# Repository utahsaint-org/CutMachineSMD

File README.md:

# CutMachineSMD

The Resistor and LED Cutting machine is a community project to make mass-production of small SMD components cut to specific unit sizes faster and easier to make for our highly popular MiniBadge initiatives and standards.  This machine has been used in mass-production and works great for feeding and cutting several component types.

#### Key Features
- SMD Tape Cutting
- Custom Menu-Driven Calibration Settings
- Test Cutting and Program Cutting
- Sharpie Attachment to allow color-coding of components as they are cut
- Community Contribution

# Parts List:  

For convenience I have an Amazon List for most parts: https://a.co/ecXTVj9

- 2020 Extruded Aluminium cut to
  - 2x 30cm - Top/Bottom
  - 3x 26cm - Verticals
  - 2x 20cm - Legs
  - 1x 155mm - Horizontal Crossmember
  - 1x 155mm - Roll Attachment Crossmember (Optional)
- 2020 Series Connectors and Corner Bracket Set (30 Piece)
- Bracket L-Type Internal Connectors for 2020 Series
- 4x 2020 Series Rubber Feet
- Stepper Motors
  - NEMA23 4.2Amp Motor (StepperOnline 23HS45-4204S)
  - NEMA17 1.2Amp Motor (StepperOnline 17HS19-2004S)
- Motor Drivers
  - 1x EASON Stepper Motor Driver TB6600 4A
  - 2x Stepper Motor Driver DRV8825
- Cutting Blades - 9mm Knife Replacement Blade Cartridge
- Electronics
  - Arduino Uno R3 or similar device.
  - HiLetgo CNC Drive Expansion Board (CNC Shield)
  - 2.42" 128x64 OLED LCD Display (SSD1309) i2C
- M3 Hardware
  - Assorted M2 Length Screws, Nuts, Washers
  - Assorted M3 Length Screws, Nuts, Washers
  - Assorted M5 Length Screws, Nuts, Washers
  - M3 Lever Steering Linkage
  - M3 Link Strut shaft 35mm
- 1x Miniature Linear Sliding Guideway Rail 150mm
- Power Supplies
  - 12VDC 15A Linear Power Supply
  - 12VDC to 5VDC Stepdown Regulator to power the Arduino (Optional)
- Components for PCBs ([Digikey](https://digikey.com)/[Mouser](https://mouser.com) or Similar)
  - 4x 6mm THT PushButton Switchs
  - 6x 10KΩ SMD  1206 Resistors
  - 1x 220Ω SMD  1206 Resistor
  - 1x 2.2KΩ SMD 1206 Resistor
  - 7+ Position Right-Angle PIN Headers
  - 3+ Position Straight PIN Headers
- PCBs Ordered (JLC_PCB or Similar)
  - [1x Button_Board](https://github.com/utahsaint-org/CutMachineSMD/tree/main/CuttingMachine_PCB/Buttons/Gerbers) 
  - [2x Sensor_Board](https://github.com/utahsaint-org/CutMachineSMD/tree/main/CuttingMachine_PCB/Sensor/Gerbers)
    
# Setup and Configuration

### OLED Screen Modification
The OLED screen typically comes configured for SPI interface, and we are using I2C protocol in this project.   As such, you will need to modify the OLED screen by bridging several solder pads to put the screen into I2C configuration.   You will need to disconnect the ribbon-cable and underneath you will need to bridge the solder pads labeled: R9, R10, R11, R12.  You will also need to remove the Resistor labeled R8. (Follow the published instructions for the screen to make this modification)

### Building the Framework
The Framework for the machine is fairly stratight-forward.  The 30cm struts are mounted as the top and bottom rails.  Use normal corner attachments to make the connections.  The 26cm vertical struts are attached with one in the middle and the other two are attached on the edges to make a 30cm x 30cm frame.  The center vertical is attached at 105mm spacing from center to center or 85mm Internal spacing.  You can use the Acrylic Cut Head mount as the spacing guide.   Lastly the cross-member can be attached at the approximate horizontal mid-point (125mm internal spacing).  20cm Legs are mounted horizontally outside the frame for stability.  The frame with mounted motors becomes back-heavy so I personally offset the legs to favor the back side for better support.

### Power Supply
Picking the right power-supply is an important aspect of any Stepper Motor configuration.   For this machine I used a 12v 15A capable power supply.   This provided all of the power I needed to run both motors and the arduino electronics.

### 3D Printing
Several of the STL designs need **supports** to be printed to ensure they are printed correctly.
NOTE: There are two Cut Heads.  One for Resistors and one for LEDs.

### Assembly
Here is what you are building:

- Build the Framework as described above.
- Attach the AcrylicCutHead on the Back Side of the machine

- Attach a RazorBlade to the Printed CutHead on the outside
  - Bottom Screw goes THRU the hole on the blade
  - Top Screw squeezes the blade to the head using a washer

- Attach the Razor CutHead to the Slider Rail
- Attach the FeedHead to the center rails (Horizontal and Vertical)
  - Align the razor to the slit of the Feedhead
- Attach and Connect the Display (See connections diagram)

### Firmware and Flashing
The Firmware is available in the repo.  Use the Arduino IDE application to program the Arduino board.  There are several sources of documentation or videos that can instruct you on how to install and use this program.  If you have issues, limited technical support is available on the <a href=https://discord.gg/saintcon>SAINTCON Discord Server</a> #minibadge-creators

You will need to install the following libraries:
- Adafruit GFX
- Adafruit SSD1306 Display

**Board Type should be Arduino Uno (R3)**

Open the *CuttingMachine_Firmware.ino* in the Arduino IDE program
Compile and upload the Firmware using the appropriate COM Port

### Connections
Connections for all of the components are outlined in the diagram below.

### PCB Boards
The PCB Boards Gerbers are included in this repo.  The following instructions will help you assemble the boards and connect them properly.

#### Button_Board
- R1, R2, R3, R4 are all **10k Ohm** resistors.
- Buttons are THT 6mm Momentary Switch.
- Right-angle PIN HEADERS are suggested exiting out the back.
- Use a Solder Jumper to connect either 5v or 3v3. (Recommended you use 3v3)
- Attach the Board with M2 Screws/Bolts to the Display Controller.
- Attach the Connectors to CNC Shield as labeled in the Connections Diagram.

#### Sensor_Board
- R1 is 10K Ohm
- R2 is 470 Ohm (if using it as presence sensor)
- R2 is 2.2K Ohm (If used as tape position sensor)
- PIN HEADERS are 3 Position
- Attach the Board with the M5 Screw to the FeedHead

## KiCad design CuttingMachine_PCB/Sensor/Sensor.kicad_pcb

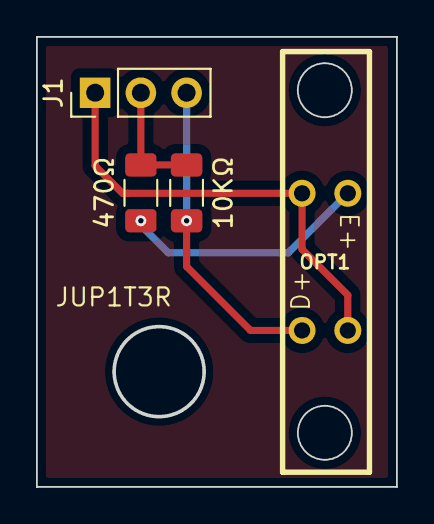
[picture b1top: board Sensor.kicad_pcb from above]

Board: 2 copper layers, 20.0 x 25.0 mm, 4 parts (0 on the bottom side), 4 nets.

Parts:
10KΩ: 220; R_1206_3216Metric_Pad1.30x1.75mm_HandSolder
470Ω: 10k; R_1206_3216Metric_Pad1.30x1.75mm_HandSolder
J1: Conn_01x03_Pin; PinHeader_1x03_P2.54mm_Vertical
OPT1: MOC7811

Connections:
unnamed: J1.1, OPT1.2 (E-), OPT1.4 (D-)
unnamed: 10KΩ.1, 470Ω.1, J1.2
unnamed: 10KΩ.2, J1.3, OPT1.3 (D+)
unnamed: 470Ω.2, OPT1.1 (E+)

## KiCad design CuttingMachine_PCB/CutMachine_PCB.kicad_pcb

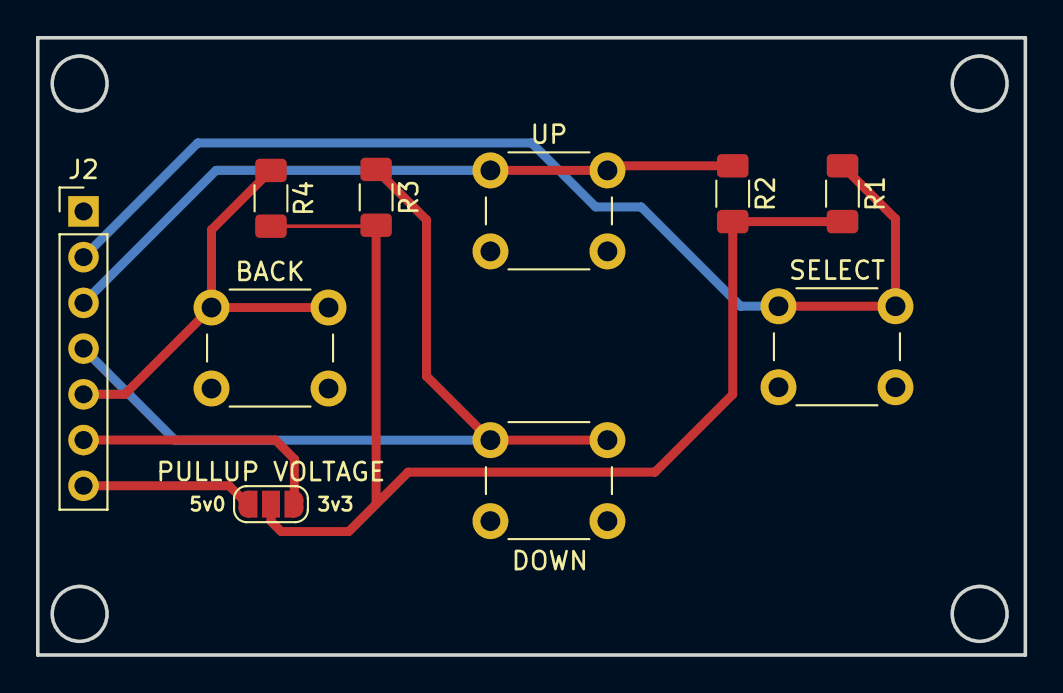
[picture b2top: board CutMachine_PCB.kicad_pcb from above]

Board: 2 copper layers, 54.9 x 34.3 mm, 10 parts (0 on the bottom side), 8 nets.

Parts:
BACK: BACK; SW_PUSH_6mm_H4.3mm
J2: Conn_01x07_Pin; PinHeader_1x07_P2.54mm_Vertical
PULLUP VOLTAGE: SolderJumper_3_Open; SolderJumper-3_P1.3mm_Open_RoundedPad1.0x1.5mm_NumberLabels
R1, R2, R3, R4: PULLUP; R_1206_3216Metric_Pad1.30x1.75mm_HandSolder
SELECT: SELECT; SW_PUSH_6mm_H4.3mm
SW3: DOWN; SW_PUSH_6mm_H4.3mm
UP: UP; SW_PUSH_6mm_H4.3mm

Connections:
+3.3V: J2.6, PULLUP VOLTAGE.3 (B)
+5V: J2.7, PULLUP VOLTAGE.1 (A)
GND: BACK.2, J2.1, SELECT.2, SW3.2, UP.2
unnamed: J2.2, R1.1, SELECT.1
unnamed: J2.3, R2.1, UP.1
unnamed: J2.4, R3.1, SW3.1
unnamed: BACK.1, J2.5, R4.1
unnamed: PULLUP VOLTAGE.2 (C), R1.2, R2.2, R3.2, R4.2

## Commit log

2024-06-09 Create CuttingMachineFW
2024-06-11 NewFW1.0.2
2024-06-11 Cleanup
2024-06-11 re-commit
2024-06-11 BasicChanges
2024-06-13 SLT and KiCAD Files
2024-06-13 LaserCut Template
    LaserCut for Acrylic object. This can also be 3D printed if needed.
2024-06-13 Framework Assembly
2024-06-17 Updates for prints
2024-06-19 Updated Firmware
2024-06-21 Updated Assets, Added Detection Sensor
2024-06-22 Fixed Navigation Stability
2024-06-22 Several UI Improvements
2024-06-22 Fixed error where display in settings menu was not working
2024-06-23 tapeLoad and other staging
2024-06-25 Documentation Update
2024-06-25 Updated Images
2024-06-28 Fixed Error in Sensor board
2024-06-29 Revert "Update CuttingMachine_Firmware.ino"
    This reverts commit 331047baca9097e741e2c189d087a95fc5961f25.
2024-06-29 Updated STL Files (Added LED Head)
2024-06-29 Fixed issue that make the settings menu not display properly.
2024-06-30 Added Reset and Sleep functions
2024-06-30 More Images
